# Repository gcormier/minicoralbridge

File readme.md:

# minicoralbridge
The goal was to try and learn a bit more about PCI. 
This card allows me to use my mini PCI-express Google Coral card in a regular PCI Express 1x slot.

In theory it will work for any type of mPCIe card that only requires 3.3 volts and uses the PCI communication lanes and no other protocols (eg SMBus)

## Kits on Tindie
I did an order of enough PCB/parts for 10 boards. I'll put the leftover 8 boards and parts up on tindie for sale
if anyone is interested : [minicoralbridge](https://www.tindie.com/products/gcormier/minicoralbridge/)

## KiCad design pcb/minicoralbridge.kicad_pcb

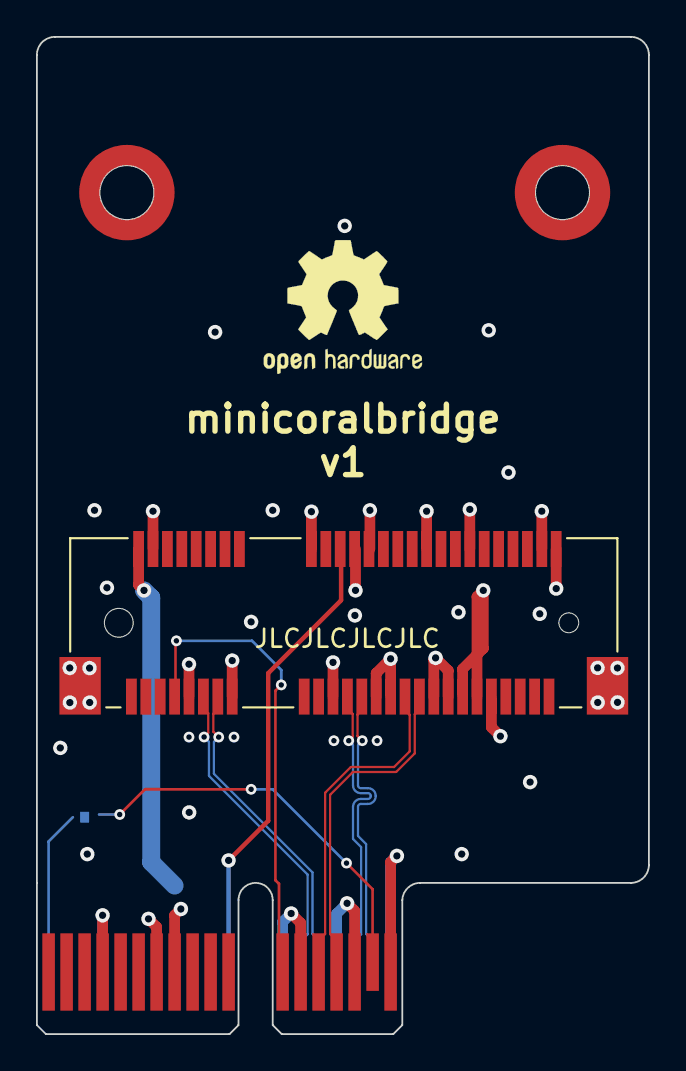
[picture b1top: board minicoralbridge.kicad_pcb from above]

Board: 4 copper layers, 34.0 x 55.4 mm, 5 parts (1 on the bottom side), 12 nets.

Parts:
H1, H2: SMSI-M2_H4mm_9774040243; Mounting_Wuerth_WA-SMSI-M2_H4mm_9774040243
J1: TE 2041262-1; BUS_PCI_Express_Mini_Half
J2: Bus_PCI_Express_x1; BUS_PCIexpress_x1
JP2: PRSNT; SolderJumper-2_P1.3mm_Bridged_RoundedPad1.0x1.5mm

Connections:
+3V3: J1.2 (+3V3AUX), J1.24 (+3V3AUX), J1.39 (+3V3AUX), J1.41 (+3V3AUX), J1.52 (+3V3AUX), J2.A9 (+3.3V), J2.A10 (+3.3V), J2.B8 (+3.3V)
/CLKREQ: J1.7 (~CLKREQ), J2.B12 (RSVD)
/MINI_PER0_N: J1.25 (PERp0), J2.A17 (PERn0)
/MINI_PER0_P: J1.23 (PERn0), J2.A16 (PERp0)
/MINI_PET0_N: J1.33 (PETp0), J2.B15 (PETn0)
/MINI_PET0_P: J1.31 (PETn0), J2.B14 (PETp0)
/MINI_REFCLK_N: J1.13 (REFCLK+), J2.A14 (REFCLK-)
/MINI_REFCLK_P: J1.11 (REFCLK-), J2.A13 (REFCLK+)
/PERST: J1.22 (~PERST), J2.A11 (~PERST)
GND: J1.4 (GND), J1.9 (GND), J1.15 (GND), J1.18 (GND), J1.21 (GND), J1.26 (GND), J1.27 (GND), J1.29 (GND), J1.34 (GND), J1.35 (GND), J1.37 (GND), J1.40 (GND), J1.43 (GND), J1.50 (GND), J2.A4 (GND), J2.A12 (GND), J2.A15 (GND), J2.A18 (GND), J2.B4 (GND), J2.B7 (GND), J2.B13 (GND), J2.B16 (GND), J2.B18 (GND)
unnamed: J2.A1 (~PRSNT1), JP2.1 (A)
unnamed: J2.B17 (~PRSNT2), JP2.2 (B)

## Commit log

2023-04-03 init
2023-04-04 more changes
2023-04-05 chchchchchanges
2023-05-21 readme
